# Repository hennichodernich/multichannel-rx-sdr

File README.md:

# A multichannel RX SDR

`hw/` contains the KiCad sources.  
`fw/` contains the Vivado 2020 project. It requires the [ADI hdl](https://github.com/analogdevicesinc/hdl/tree/2021_r1) repo.  
`sw/` contains the Petalinux driver sources and an example DTSI.  

Consider this work in progress.  

On the host side, you'll need [my gr-iio blocks](https://github.com/hennichodernich/gr-iio).

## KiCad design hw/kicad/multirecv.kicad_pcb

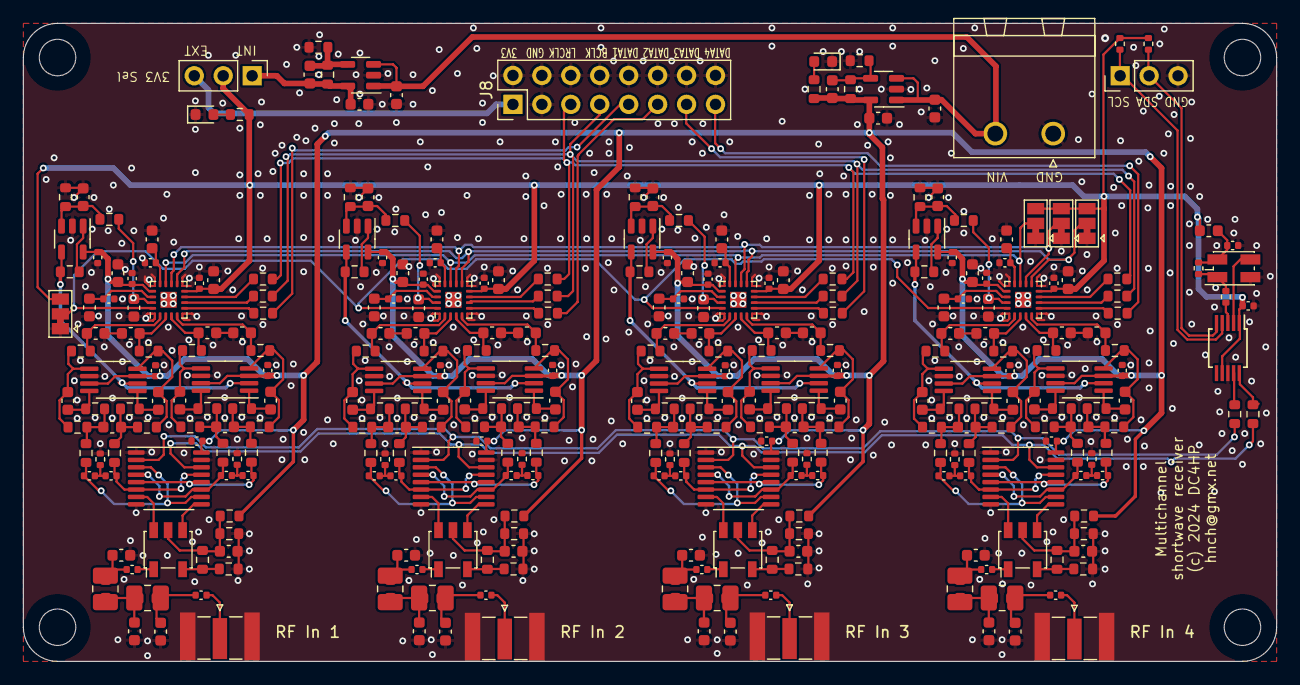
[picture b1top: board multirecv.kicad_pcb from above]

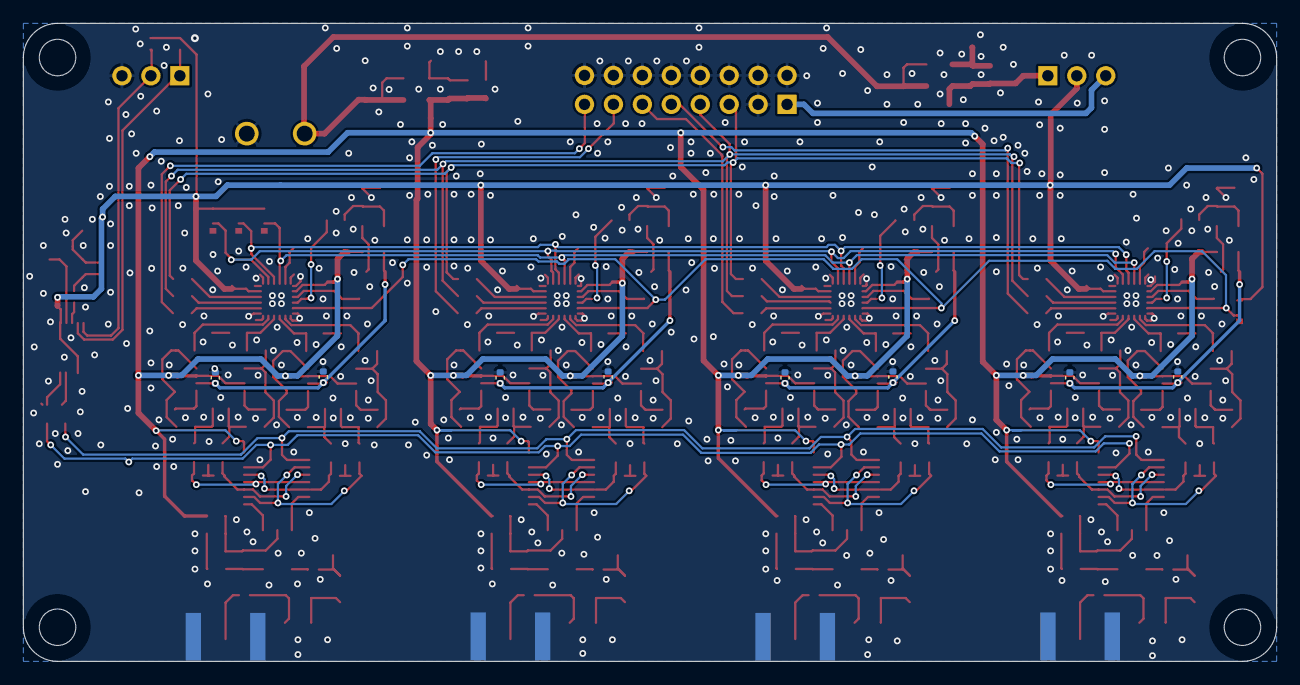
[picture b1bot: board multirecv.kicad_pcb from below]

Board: 2 copper layers, 110.0 x 56.0 mm, 331 parts (8 on the bottom side), 190 nets.

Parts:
C1, C2, C16, C17, C60, C61, C69, C70, C114, C115, C123, C124, C132, C133, C141, C142: np; C_0402_1005Metric
C3, C18, C62, C71, C116, C125, C134, C143: 180p; C_0603_1608Metric
C4, C5, C19, C20, C63, C64, C72, C73, C117, C118, C126, C127, C135, C136, C144, C145: 36p; C_0603_1608Metric
C6, C7, C9, C10, C15, C21, C22, C23, C26, C28, C30, C33, C34, C36, C38, C47, C48, C49, C50, C51, C56, C59, C65, C66, C74, C75, C78, C83, C84, C85, C86, C87, C92, C95, C96, C101, C102, C103, C104, C105, C110, C113, C119, C120, C128, C129, C137, C138, C146, C147: 100n; C_0402_1005Metric
C8, C12, C24, C25, C67, C68, C76, C77, C121, C122, C130, C131, C139, C140, C148, C149: 2.2n; C_0603_1608Metric
C11, C14, C32, C42, C44, C53, C80, C89, C98, C107, C150, C152: 2.2u; C_0603_1608Metric
C13, C27, C29, C31, C43, C45, C46, C79, C81, C82, C97, C99, C100, C151: np; C_0603_1608Metric
C35, C39, C52, C57, C88, C93, C106, C111: 1u; C_0603_1608Metric
C37, C40, C41, C54, C55, C58, C90, C91, C94, C108, C109, C112: 10u; C_0603_1608Metric
D1, D2: LED; LED_0603_1608Metric
FB1: FerriteBead; L_0603_1608Metric
H1, H2, H3, H4: MountingHole; MountingHole_3.2mm_M3_DIN965
J1, J4, J5, J6: Conn_Coaxial; SMA_Samtec_SMA-J-P-X-ST-EM1_EdgeMount
J2: Conn_01x03; PinHeader_1x03_P2.54mm_Vertical
J3: Conn_01x02_Male; PhoenixContact_MSTBA_2,5_2-G-5,08_1x02_P5.08mm_Horizontal
J8: Conn_02x08_Odd_Even; PinHeader_2x08_P2.54mm_Vertical
JP1, JP2, JP3, JP4: Jumper_3_Bridged12; SolderJumper-3_P1.3mm_Bridged12_Pad1.0x1.5mm
JP5: Jumper_3_Open; PinHeader_1x03_P2.54mm_Vertical
L1, L2, L3, L4, L5, L6, L7, L8: 0; L_1008_0805_0603_HandSolder_Combo
R1, R22, R50, R59, R88, R97, R106, R115: 0; R_0402_1005Metric
R2, R4, R15, R23, R24, R51, R52, R60, R61, R89, R90, R98, R99, R107, R108, R116, R117, R126: 1k; R_0603_1608Metric
R3, R7, R8: 4.7k; R_0402_1005Metric
R5: np; R_0402_1005Metric
R6, R17, R25, R26, R53, R54, R62, R63, R91, R92, R100, R101, R109, R110, R118, R119: 4.02k; R_0603_1608Metric
R10, R12: 22; R_0603_1608Metric
R13, R14, R34, R39, R71, R81, R124, R125: np; R_0603_1608Metric
R16, R40, R72, R82: 10; R_0603_1608Metric
R18, R19, R27, R28, R55, R56, R64, R65, R93, R94, R102, R103, R111, R112, R120, R121: 806; R_0603_1608Metric
R20, R21, R29, R30, R57, R58, R66, R67, R95, R96, R104, R105, R113, R114, R122, R123: 27; R_0603_1608Metric
R31, R32, R35, R36, R41, R43, R48, R49, R68, R69, R73, R74, R78, R79, R83, R84: 10k; R_0603_1608Metric
R33, R38, R70, R80: 0; R_0603_1608Metric
R37, R42, R44, R45, R46, R47, R75, R76, R77, R85, R86, R87: 33; R_0603_1608Metric
TR1, TR2, TR3, TR4: ETC4-1-2; Transformer_MACOM_SM-22
U1: Si5351A-B-GT; MSOP-10_3x3mm_P0.5mm
U2, U5, U11, U12, U19, U20, U21, U22: MCP6D11/MS; MSOP-8_3x3mm_P0.65mm
U3, U23: LP5907-3.3; SOT-23-5
U4, U9, U14, U17: MCP6401-xOT; SOT-23-5
U6, U8, U13, U16: SN74CBT3253; TSSOP-16_4.4x5mm_P0.65mm
U7, U10, U15, U18: PCM1820; BurrBrown_WQFN-20-1EP_2.8x2.8mm_P0.5mm_EP1.4x1.4mm
X1: XO53; Oscillator_SMD_EuroQuartz_XO32-4Pin_3.2x2.5mm_HandSoldering

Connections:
3V3_EXT: J8.1, JP5.3 (B)
+3V3: C10.1, C30.1, C40.1, C58.1, C59.1, C94.1, C95.1, C112.1, C113.1, FB1.1, JP1.3 (B), JP2.3 (B), JP3.3 (B), JP4.3 (B), JP5.2 (C), R7.2, R8.2, R126.1, U1.1 (VDD), U1.7 (VDDO), U7.9 (IOVDD), U10.9 (IOVDD), U15.9 (IOVDD), U18.9 (IOVDD)
/Channel1/DIN: J8.13, R46.2
/Channel1/RFin: C22.2, J4.1 (In)
/Channel1/diffamp1/IN+: C70.2, R60.2, U8.4 (1B3), U8.11 (2B2)
/Channel1/diffamp1/IN-: C69.1, R61.2, U8.5 (1B2), U8.12 (2B3)
/Channel1/diffamp1/OUT+: C76.2, R66.1, U10.4 (IN2-)
/Channel1/diffamp1/OUT-: C77.1, R67.1, U10.3 (IN2+)
/Channel1/diffamp/IN+: C61.2, R51.2, U8.3 (1B4), U8.10 (2B1)
/Channel1/diffamp/IN-: C60.1, R52.2, U8.6 (1B1), U8.13 (2B4)
/Channel1/diffamp/OUT+: C67.2, R57.1, U10.2 (IN1L-)
/Channel1/diffamp/OUT-: C68.1, R58.1, U10.1 (IN1+)
/Channel1/diffamp/VOCM: C65.1, C74.1, R40.1, U9.4 (-), U11.2 (VOCM), U12.2 (VOCM)
/Channel2/DIN: J8.9, R87.2
/Channel2/RFin: C96.2, J5.1 (In)
/Channel2/diffamp1/IN+: C133.2, R107.2, U16.4 (1B3), U16.11 (2B2)
/Channel2/diffamp1/IN-: C132.1, R108.2, U16.5 (1B2), U16.12 (2B3)
/Channel2/diffamp1/OUT+: C139.2, R113.1, U18.4 (IN2-)
/Channel2/diffamp1/OUT-: C140.1, R114.1, U18.3 (IN2+)
/Channel2/diffamp/IN+: C124.2, R98.2, U16.3 (1B4), U16.10 (2B1)
/Channel2/diffamp/IN-: C123.1, R99.2, U16.6 (1B1), U16.13 (2B4)
/Channel2/diffamp/OUT+: C130.2, R104.1, U18.2 (IN1L-)
/Channel2/diffamp/OUT-: C131.1, R105.1, U18.1 (IN1+)
/Channel2/diffamp/VOCM: C128.1, C137.1, R82.1, U17.4 (-), U20.2 (VOCM), U21.2 (VOCM)
/Channel3/DIN: J8.11, R77.2
/Channel3/RFin: C78.2, J6.1 (In)
/Channel3/diffamp1/IN+: C142.2, R116.2, U13.4 (1B3), U13.11 (2B2)
/Channel3/diffamp1/IN-: C141.1, R117.2, U13.5 (1B2), U13.12 (2B3)
/Channel3/diffamp1/OUT+: C148.2, R122.1, U15.4 (IN2-)
/Channel3/diffamp1/OUT-: C149.1, R123.1, U15.3 (IN2+)
/Channel3/diffamp/IN+: C115.2, R89.2, U13.3 (1B4), U13.10 (2B1)
/Channel3/diffamp/IN-: C114.1, R90.2, U13.6 (1B1), U13.13 (2B4)
/Channel3/diffamp/OUT+: C121.2, R95.1, U15.2 (IN1L-)
/Channel3/diffamp/OUT-: C122.1, R96.1, U15.1 (IN1+)
/Channel3/diffamp/VOCM: C119.1, C146.1, R72.1, U14.4 (-), U19.2 (VOCM), U22.2 (VOCM)
/Channel/BCLK: J8.7, R37.2, R44.2, R75.2, R85.2
/Channel/CONF1: JP1.2 (C), U7.19 (FMT0), U10.19 (FMT0), U15.19 (FMT0), U18.19 (FMT0)
/Channel/CONF2: JP2.2 (C), U7.11 (MD1), U10.11 (MD1), U15.11 (MD1), U18.11 (MD1)
/Channel/CONF3: JP3.2 (C), U7.12 (MD0), U10.12 (MD0), U15.12 (MD0), U18.12 (MD0)
/Channel/CONF4: JP4.2 (C), U7.13 (MSZ), U10.13 (MSZ), U15.13 (MSZ), U18.13 (MSZ)
/Channel/DIN: J8.15, R47.2
/Channel/LRCLK: J8.5, R42.2, R45.2, R76.2, R86.2
/Channel/RFin: C26.2, J1.1 (In)
/Channel/diffamp1/IN+: C17.2, R23.2, U6.4 (1B3), U6.11 (2B2)
/Channel/diffamp1/IN-: C16.1, R24.2, U6.5 (1B2), U6.12 (2B3)
/Channel/diffamp1/OUT+: C24.2, R29.1, U7.4 (IN2-)
/Channel/diffamp1/OUT-: C25.1, R30.1, U7.3 (IN2+)
/Channel/diffamp/IN+: C2.2, R2.2, U6.3 (1B4), U6.10 (2B1)
/Channel/diffamp/IN-: C1.1, R4.2, U6.6 (1B1), U6.13 (2B4)
/Channel/diffamp/OUT+: C8.2, R20.1, U7.2 (IN1L-)
/Channel/diffamp/OUT-: C12.1, R21.1, U7.1 (IN1+)
/Channel/diffamp/VOCM: C6.1, C21.1, R16.1, U2.2 (VOCM), U4.4 (-), U5.2 (VOCM)
/SCL: J2.1, R8.1, U1.4 (SCL)
/SDA: J2.2, R7.1, U1.5 (SDA)
CLK0: R10.2, U6.14 (S0), U8.14 (S0), U13.14 (S0), U16.14 (S0)
CLK1: R12.2, U6.2 (S1), U8.2 (S1), U13.2 (S1), U16.2 (S1)
GND: C6.2, C7.2, C8.1, C9.2, C10.2, C11.2, C12.2, C14.2, C15.2, C21.2, C23.2, C24.1, C25.2, C27.1, C28.2, C29.1, C30.2, C31.1, C32.2, C34.2, C35.1, C36.2, C37.2, C38.2, C39.2, C40.2, C41.2, C42.2, C43.1, C44.2, C45.1, C46.1, C48.2, C49.2, C50.2, C51.2, C52.1, C53.2, C54.2, C55.2, C56.2, C57.2, C58.2, C59.2, C65.2, C66.2, C67.1, C68.2, C74.2, C75.2, C76.1, C77.2, C79.1, C80.2, C81.1, C82.1, C84.2, C85.2, C86.2, C87.2, C88.1, C89.2, C90.2, C91.2, C92.2, C93.2, C94.2, C95.2, C97.1, C98.2, C99.1, C100.1, C102.2, C103.2, C104.2, C105.2, C106.1, C107.2, C108.2, C109.2, C110.2, C111.2, C112.2, C113.2, C119.2, C120.2, C121.1, C122.2, C128.2, C129.2, C130.1, C131.2, C137.2, C138.2, C139.1, C140.2, C146.2, C147.2, C148.1, C149.2, C150.2, C152.2, D1.1 (K), D2.1 (K), J1.2 (Ext), J2.3, J3.1, J4.2 (Ext), J5.2 (Ext), J6.2 (Ext), J8.2, J8.3, J8.4, J8.6, J8.8, J8.10, J8.12, J8.14, J8.16, JP1.1 (A), JP2.1 (A), JP3.1 (A), JP4.1 (A), R1.1, R14.2, R22.1, R32.2, R33.2, R36.2, R38.2, R43.2, R49.2, R50.1, R59.1, R69.2, R70.2, R74.2, R79.2, R80.2, R84.2, R88.1, R97.1, R106.1, R115.1, R125.2, U1.8 (GND), U2.6 (V-), U3.2 (GND), U4.2 (V-), U5.6 (V-), U6.1 (1~OE), U6.8 (GND), U6.15 (2~OE), U7.5 (VSS), U7.10 (VSS), U7.15 (VSS), U7.20 (VSS), U7.EP (VSS), U8.1 (1~OE), U8.8 (GND), U8.15 (2~OE), U9.2 (V-), U10.5 (VSS), U10.10 (VSS), U10.15 (VSS), U10.20 (VSS), U10.EP (VSS), U11.6 (V-), U12.6 (V-), U13.1 (1~OE), U13.8 (GND), U13.15 (2~OE), U14.2 (V-), U15.5 (VSS), U15.10 (VSS), U15.15 (VSS), U15.20 (VSS), U15.EP (VSS), U16.1 (1~OE), U16.8 (GND), U16.15 (2~OE), U17.2 (V-), U18.5 (VSS), U18.10 (VSS), U18.15 (VSS), U18.20 (VSS), U18.EP (VSS), U19.6 (V-), U20.6 (V-), U21.6 (V-), U22.6 (V-), U23.2 (GND), X1.2 (GND)
unnamed: C1.2, C2.1, R1.2
unnamed: C3.1, R2.1, R17.2, R18.2
unnamed: C3.2, R4.1, R6.1, R19.1
unnamed: C16.2, C17.1, R22.2
unnamed: C18.1, R23.1, R26.2, R27.2
unnamed: C18.2, R24.1, R25.1, R28.1
unnamed: C22.1, C43.2, L1.2
unnamed: C26.1, C27.2, L2.2
unnamed: C29.2, L2.1, L4.1
unnamed: C31.2, C33.2, L4.2
unnamed: C32.1, R31.2, R32.1, R34.2, TR1.4
unnamed: C33.1, TR1.1
unnamed: C44.1, R35.2, R36.1, R39.2, TR2.4
unnamed: C45.2, L1.1, L3.1
unnamed: C46.2, C47.2, L3.2
unnamed: C47.1, TR2.1
unnamed: C60.2, C61.1, R50.2
unnamed: C62.1, R51.1, R54.2, R55.2
unnamed: C62.2, R52.1, R53.1, R56.1
unnamed: C69.2, C70.1, R59.2
unnamed: C71.1, R60.1, R63.2, R64.2
unnamed: C71.2, R61.1, R62.1, R65.1
unnamed: C78.1, C79.2, L5.2
unnamed: C80.1, R68.2, R69.1, R71.2, TR3.4
unnamed: C81.2, L5.1, L6.1
unnamed: C82.2, C83.2, L6.2
unnamed: C83.1, TR3.1
unnamed: C96.1, C97.2, L7.2
unnamed: C98.1, R78.2, R79.1, R81.2, TR4.4
unnamed: C99.2, L7.1, L8.1
unnamed: C100.2, C101.2, L8.2
unnamed: C101.1, TR4.1
unnamed: C114.2, C115.1, R88.2
unnamed: C116.1, R89.1, R92.2, R93.2
unnamed: C116.2, R90.1, R91.1, R94.1
unnamed: C123.2, C124.1, R97.2
unnamed: C125.1, R98.1, R101.2, R102.2
unnamed: C125.2, R99.1, R100.1, R103.1
unnamed: C132.2, C133.1, R106.2
unnamed: C134.1, R107.1, R110.2, R111.2
unnamed: C134.2, R108.1, R109.1, R112.1
unnamed: C141.2, C142.1, R115.2
unnamed: C143.1, R116.1, R119.2, R120.2
unnamed: C143.2, R117.1, R118.1, R121.1
unnamed: D1.2 (A), R15.2
unnamed: D2.2 (A), R126.2
unnamed: C151.1, C152.1, JP5.1 (A), R124.1, U23.5 (OUT)
unnamed: R16.2, U4.1
unnamed: R33.1, R34.1, TR1.2
unnamed: R38.1, R39.1, TR2.2
unnamed: R40.2, U9.1
unnamed: R70.1, R71.1, TR3.2
unnamed: R72.2, U14.1
unnamed: R80.1, R81.1, TR4.2
unnamed: R82.2, U17.1
unnamed: R10.1, U1.10 (CLK0)
unnamed: R12.1, U1.9 (CLK1)
unnamed: U1.2 (XA), X1.3 (OUT)
unnamed: R5.2, U1.3 (XB)
unnamed: C5.2, R18.1, U2.8 (VIN+)
unnamed: C4.1, R19.2, U2.1 (VIN-)
unnamed: C4.2, R6.2, R20.2, U2.4 (VOUT+)
unnamed: C5.1, R17.1, R21.2, U2.5 (VOUT-)
unnamed: C13.2, R13.2, R14.1, U3.4 (NR)
unnamed: C42.1, R48.2, R49.1, U4.3 (+)
unnamed: C20.2, R27.1, U5.8 (VIN+)
unnamed: C19.1, R28.2, U5.1 (VIN-)
unnamed: C19.2, R25.2, R29.2, U5.4 (VOUT+)
unnamed: C20.1, R26.1, R30.2, U5.5 (VOUT-)
unnamed: TR1.5, U6.7 (1A)
unnamed: TR1.3, U6.9 (2A)
unnamed: C37.1, C38.1, U7.17 (AREG)
unnamed: R37.1, U7.7 (BCLK)
unnamed: C36.1, C41.1, U7.14 (DREG)
unnamed: R42.1, U7.8 (FCLK)
unnamed: R47.1, U7.6 (SDOUT)
unnamed: C35.2, R48.1, U7.18 (VREF)
unnamed: TR2.5, U8.7 (1A)
unnamed: TR2.3, U8.9 (2A)
unnamed: C53.1, R41.2, R43.1, U9.3 (+)
unnamed: C50.1, C54.1, U10.17 (AREG)
unnamed: R44.1, U10.7 (BCLK)
unnamed: C51.1, C55.1, U10.14 (DREG)
unnamed: R45.1, U10.8 (FCLK)
unnamed: R46.1, U10.6 (SDOUT)
unnamed: C52.2, R41.1, U10.18 (VREF)
unnamed: C64.2, R55.1, U11.8 (VIN+)
unnamed: C63.1, R56.2, U11.1 (VIN-)
unnamed: C63.2, R53.2, R57.2, U11.4 (VOUT+)
unnamed: C64.1, R54.1, R58.2, U11.5 (VOUT-)
unnamed: C73.2, R64.1, U12.8 (VIN+)
unnamed: C72.1, R65.2, U12.1 (VIN-)
unnamed: C72.2, R62.2, R66.2, U12.4 (VOUT+)
unnamed: C73.1, R63.1, R67.2, U12.5 (VOUT-)
unnamed: TR3.5, U13.7 (1A)
unnamed: TR3.3, U13.9 (2A)
unnamed: C89.1, R73.2, R74.1, U14.3 (+)
unnamed: C86.1, C90.1, U15.17 (AREG)
unnamed: R75.1, U15.7 (BCLK)
unnamed: C87.1, C91.1, U15.14 (DREG)
unnamed: R76.1, U15.8 (FCLK)
unnamed: R77.1, U15.6 (SDOUT)
unnamed: C88.2, R73.1, U15.18 (VREF)
unnamed: TR4.5, U16.7 (1A)
unnamed: TR4.3, U16.9 (2A)
unnamed: C107.1, R83.2, R84.1, U17.3 (+)
unnamed: C104.1, C108.1, U18.17 (AREG)
unnamed: R85.1, U18.7 (BCLK)
unnamed: C105.1, C109.1, U18.14 (DREG)
unnamed: R86.1, U18.8 (FCLK)
unnamed: R87.1, U18.6 (SDOUT)
unnamed: C106.2, R83.1, U18.18 (VREF)
unnamed: C118.2, R93.1, U19.8 (VIN+)
unnamed: C117.1, R94.2, U19.1 (VIN-)
unnamed: C117.2, R91.2, R95.2, U19.4 (VOUT+)
unnamed: C118.1, R92.1, R96.2, U19.5 (VOUT-)
unnamed: C127.2, R102.1, U20.8 (VIN+)
unnamed: C126.1, R103.2, U20.1 (VIN-)
unnamed: C126.2, R100.2, R104.2, U20.4 (VOUT+)
unnamed: C127.1, R101.1, R105.2, U20.5 (VOUT-)
unnamed: C136.2, R111.1, U21.8 (VIN+)
unnamed: C135.1, R112.2, U21.1 (VIN-)
unnamed: C135.2, R109.2, R113.2, U21.4 (VOUT+)
unnamed: C136.1, R110.1, R114.2, U21.5 (VOUT-)
unnamed: C145.2, R120.1, U22.8 (VIN+)
unnamed: C144.1, R121.2, U22.1 (VIN-)
unnamed: C144.2, R118.2, R122.2, U22.4 (VOUT+)
unnamed: C145.1, R119.1, R123.2, U22.5 (VOUT-)
unnamed: C151.2, R124.2, R125.1, U23.4 (NR)
unnamed: R3.2, R5.1, X1.1 (EN)
unnamed: C9.1, FB1.2, R3.1, X1.4 (V+)
VAA: C7.1, C13.1, C14.1, C15.1, C23.1, C28.1, C34.1, C39.1, C48.1, C49.1, C56.1, C57.1, C66.1, C75.1, C84.1, C85.1, C92.1, C93.1, C102.1, C103.1, C110.1, C111.1, C120.1, C129.1, C138.1, C147.1, R13.1, R15.1, R31.1, R35.1, R68.1, R78.1, U2.3 (V+), U2.7 (~PD), U3.5 (OUT), U4.5 (V+), U5.3 (V+), U5.7 (~PD), U6.16 (VCC), U7.16 (AVDD), U8.16 (VCC), U9.5 (V+), U10.16 (AVDD), U11.3 (V+), U11.7 (~PD), U12.3 (V+), U12.7 (~PD), U13.16 (VCC), U14.5 (V+), U15.16 (AVDD), U16.16 (VCC), U17.5 (V+), U18.16 (AVDD), U19.3 (V+), U19.7 (~PD), U20.3 (V+), U20.7 (~PD), U21.3 (V+), U21.7 (~PD), U22.3 (V+), U22.7 (~PD)
VIN: C11.1, C150.1, J3.2, U3.1 (IN), U3.3 (EN), U23.1 (IN), U23.3 (EN)

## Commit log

2025-08-03 Initial commit.
2025-08-03 Added missing DTSI.
2025-08-03 Added README
2025-08-03 Fixed typo in README

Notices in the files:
hw/kicad/multirecv.kicad_pcb:
(c) 2024 DC4HP
